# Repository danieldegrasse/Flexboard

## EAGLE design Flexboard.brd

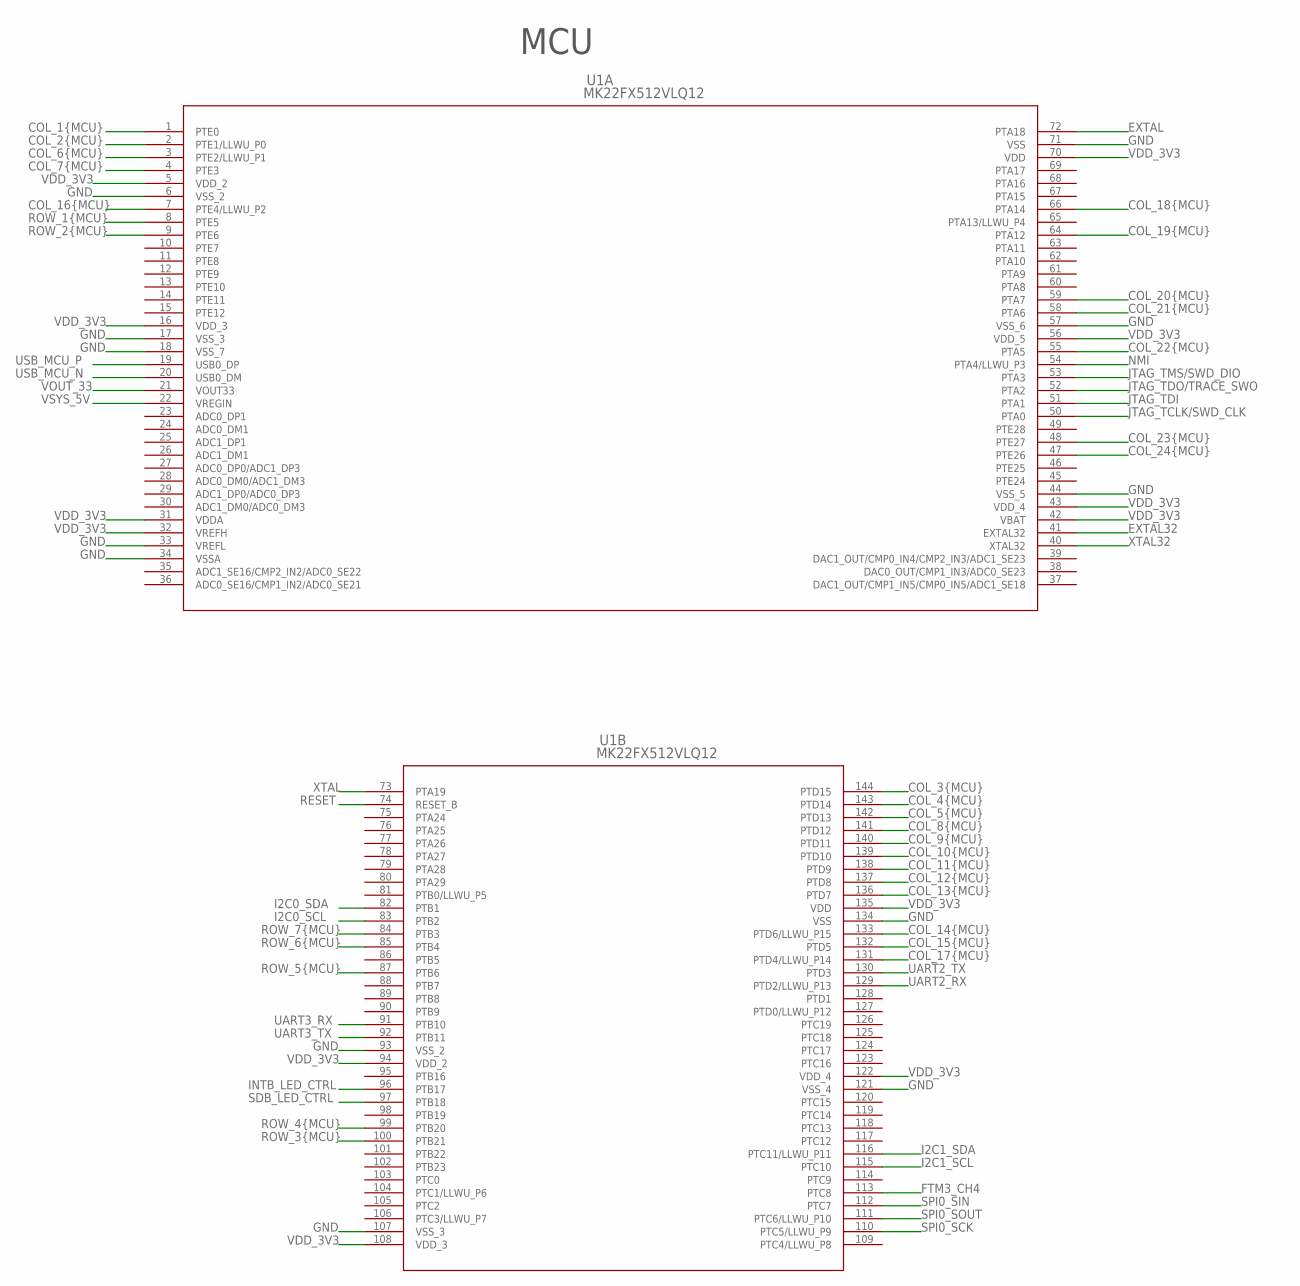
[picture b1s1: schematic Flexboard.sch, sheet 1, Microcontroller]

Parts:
U1: MK22FX512VLQ12; LQFP-144_20X20X1.6

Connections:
COL_1{MCU}: U1.1 (PTE0); also elsewhere on the board
COL_2{MCU}: U1.2 (PTE1/LLWU_P0); also elsewhere on the board
COL_3{MCU}: U1.144 (PTD15); also elsewhere on the board
COL_4{MCU}: U1.143 (PTD14); also elsewhere on the board
COL_5{MCU}: U1.142 (PTD13); also elsewhere on the board
COL_6{MCU}: U1.3 (PTE2/LLWU_P1); also elsewhere on the board
COL_7{MCU}: U1.4 (PTE3); also elsewhere on the board
COL_8{MCU}: U1.141 (PTD12); also elsewhere on the board
COL_9{MCU}: U1.140 (PTD11); also elsewhere on the board
COL_10{MCU}: U1.139 (PTD10); also elsewhere on the board
COL_11{MCU}: U1.138 (PTD9); also elsewhere on the board
COL_12{MCU}: U1.137 (PTD8); also elsewhere on the board
COL_13{MCU}: U1.136 (PTD7); also elsewhere on the board
COL_14{MCU}: U1.133 (PTD6/LLWU_P15); also elsewhere on the board
COL_15{MCU}: U1.132 (PTD5); also elsewhere on the board
COL_16{MCU}: U1.7 (PTE4/LLWU_P2); also elsewhere on the board
COL_17{MCU}: U1.131 (PTD4/LLWU_P14); also elsewhere on the board
COL_18{MCU}: U1.66 (PTA14); also elsewhere on the board
COL_19{MCU}: U1.64 (PTA12); also elsewhere on the board
COL_20{MCU}: U1.59 (PTA7); also elsewhere on the board
COL_21{MCU}: U1.58 (PTA6); also elsewhere on the board
COL_22{MCU}: U1.55 (PTA5); also elsewhere on the board
COL_23{MCU}: U1.48 (PTE27); also elsewhere on the board
COL_24{MCU}: U1.47 (PTE26); also elsewhere on the board
EXTAL: U1.72 (PTA18); also elsewhere on the board
EXTAL32: U1.41 (EXTAL32); also elsewhere on the board
FTM3_CH4: U1.113 (PTC8); also elsewhere on the board
GND: U1.6 (VSS_2), U1.17 (VSS_3), U1.18 (VSS_7), U1.33 (VREFL), U1.34 (VSSA), U1.44 (VSS_5), U1.57 (VSS_6), U1.71 (VSS), U1.93 (VSS_2), U1.107 (VSS_3), U1.121 (VSS_4), U1.134 (VSS); also elsewhere on the board
I2C0_SCL: U1.83 (PTB2); also elsewhere on the board
I2C0_SDA: U1.82 (PTB1); also elsewhere on the board
I2C1_SCL: U1.115 (PTC10); also elsewhere on the board
I2C1_SDA: U1.116 (PTC11/LLWU_P11); also elsewhere on the board
INTB_LED_CTRL: U1.96 (PTB17); also elsewhere on the board
JTAG_TCLK/SWD_CLK: U1.50 (PTA0); also elsewhere on the board
JTAG_TDI: U1.51 (PTA1); also elsewhere on the board
JTAG_TDO/TRACE_SWO: U1.52 (PTA2); also elsewhere on the board
JTAG_TMS/SWD_DIO: U1.53 (PTA3); also elsewhere on the board
NMI: U1.54 (PTA4/LLWU_P3); also elsewhere on the board
RESET: U1.74 (RESET_B); also elsewhere on the board
ROW_1{MCU}: U1.8 (PTE5); also elsewhere on the board
ROW_2{MCU}: U1.9 (PTE6); also elsewhere on the board
ROW_3{MCU}: U1.100 (PTB21); also elsewhere on the board
ROW_4{MCU}: U1.99 (PTB20); also elsewhere on the board
ROW_5{MCU}: U1.87 (PTB6); also elsewhere on the board
ROW_6{MCU}: U1.85 (PTB4); also elsewhere on the board
ROW_7{MCU}: U1.84 (PTB3); also elsewhere on the board
SDB_LED_CTRL: U1.97 (PTB18); also elsewhere on the board
SPI0_SCK: U1.110 (PTC5/LLWU_P9); also elsewhere on the board
SPI0_SIN: U1.112 (PTC7); also elsewhere on the board
SPI0_SOUT: U1.111 (PTC6/LLWU_P10); also elsewhere on the board
UART2_RX: U1.129 (PTD2/LLWU_P13); also elsewhere on the board
UART2_TX: U1.130 (PTD3); also elsewhere on the board
UART3_RX: U1.91 (PTB10); also elsewhere on the board
UART3_TX: U1.92 (PTB11); also elsewhere on the board
USB_MCU_N: U1.20 (USB0_DM); also elsewhere on the board
USB_MCU_P: U1.19 (USB0_DP); also elsewhere on the board
VDD_3V3: U1.5 (VDD_2), U1.16 (VDD_3), U1.31 (VDDA), U1.32 (VREFH), U1.42 (VBAT), U1.43 (VDD_4), U1.56 (VDD_5), U1.70 (VDD), U1.94 (VDD_2), U1.108 (VDD_3), U1.122 (VDD_4), U1.135 (VDD); also elsewhere on the board
VOUT_33: U1.21 (VOUT33); also elsewhere on the board
VSYS_5V: U1.22 (VREGIN); also elsewhere on the board
XTAL: U1.73 (PTA19); also elsewhere on the board
XTAL32: U1.40 (XTAL32); also elsewhere on the board

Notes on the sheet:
MCU

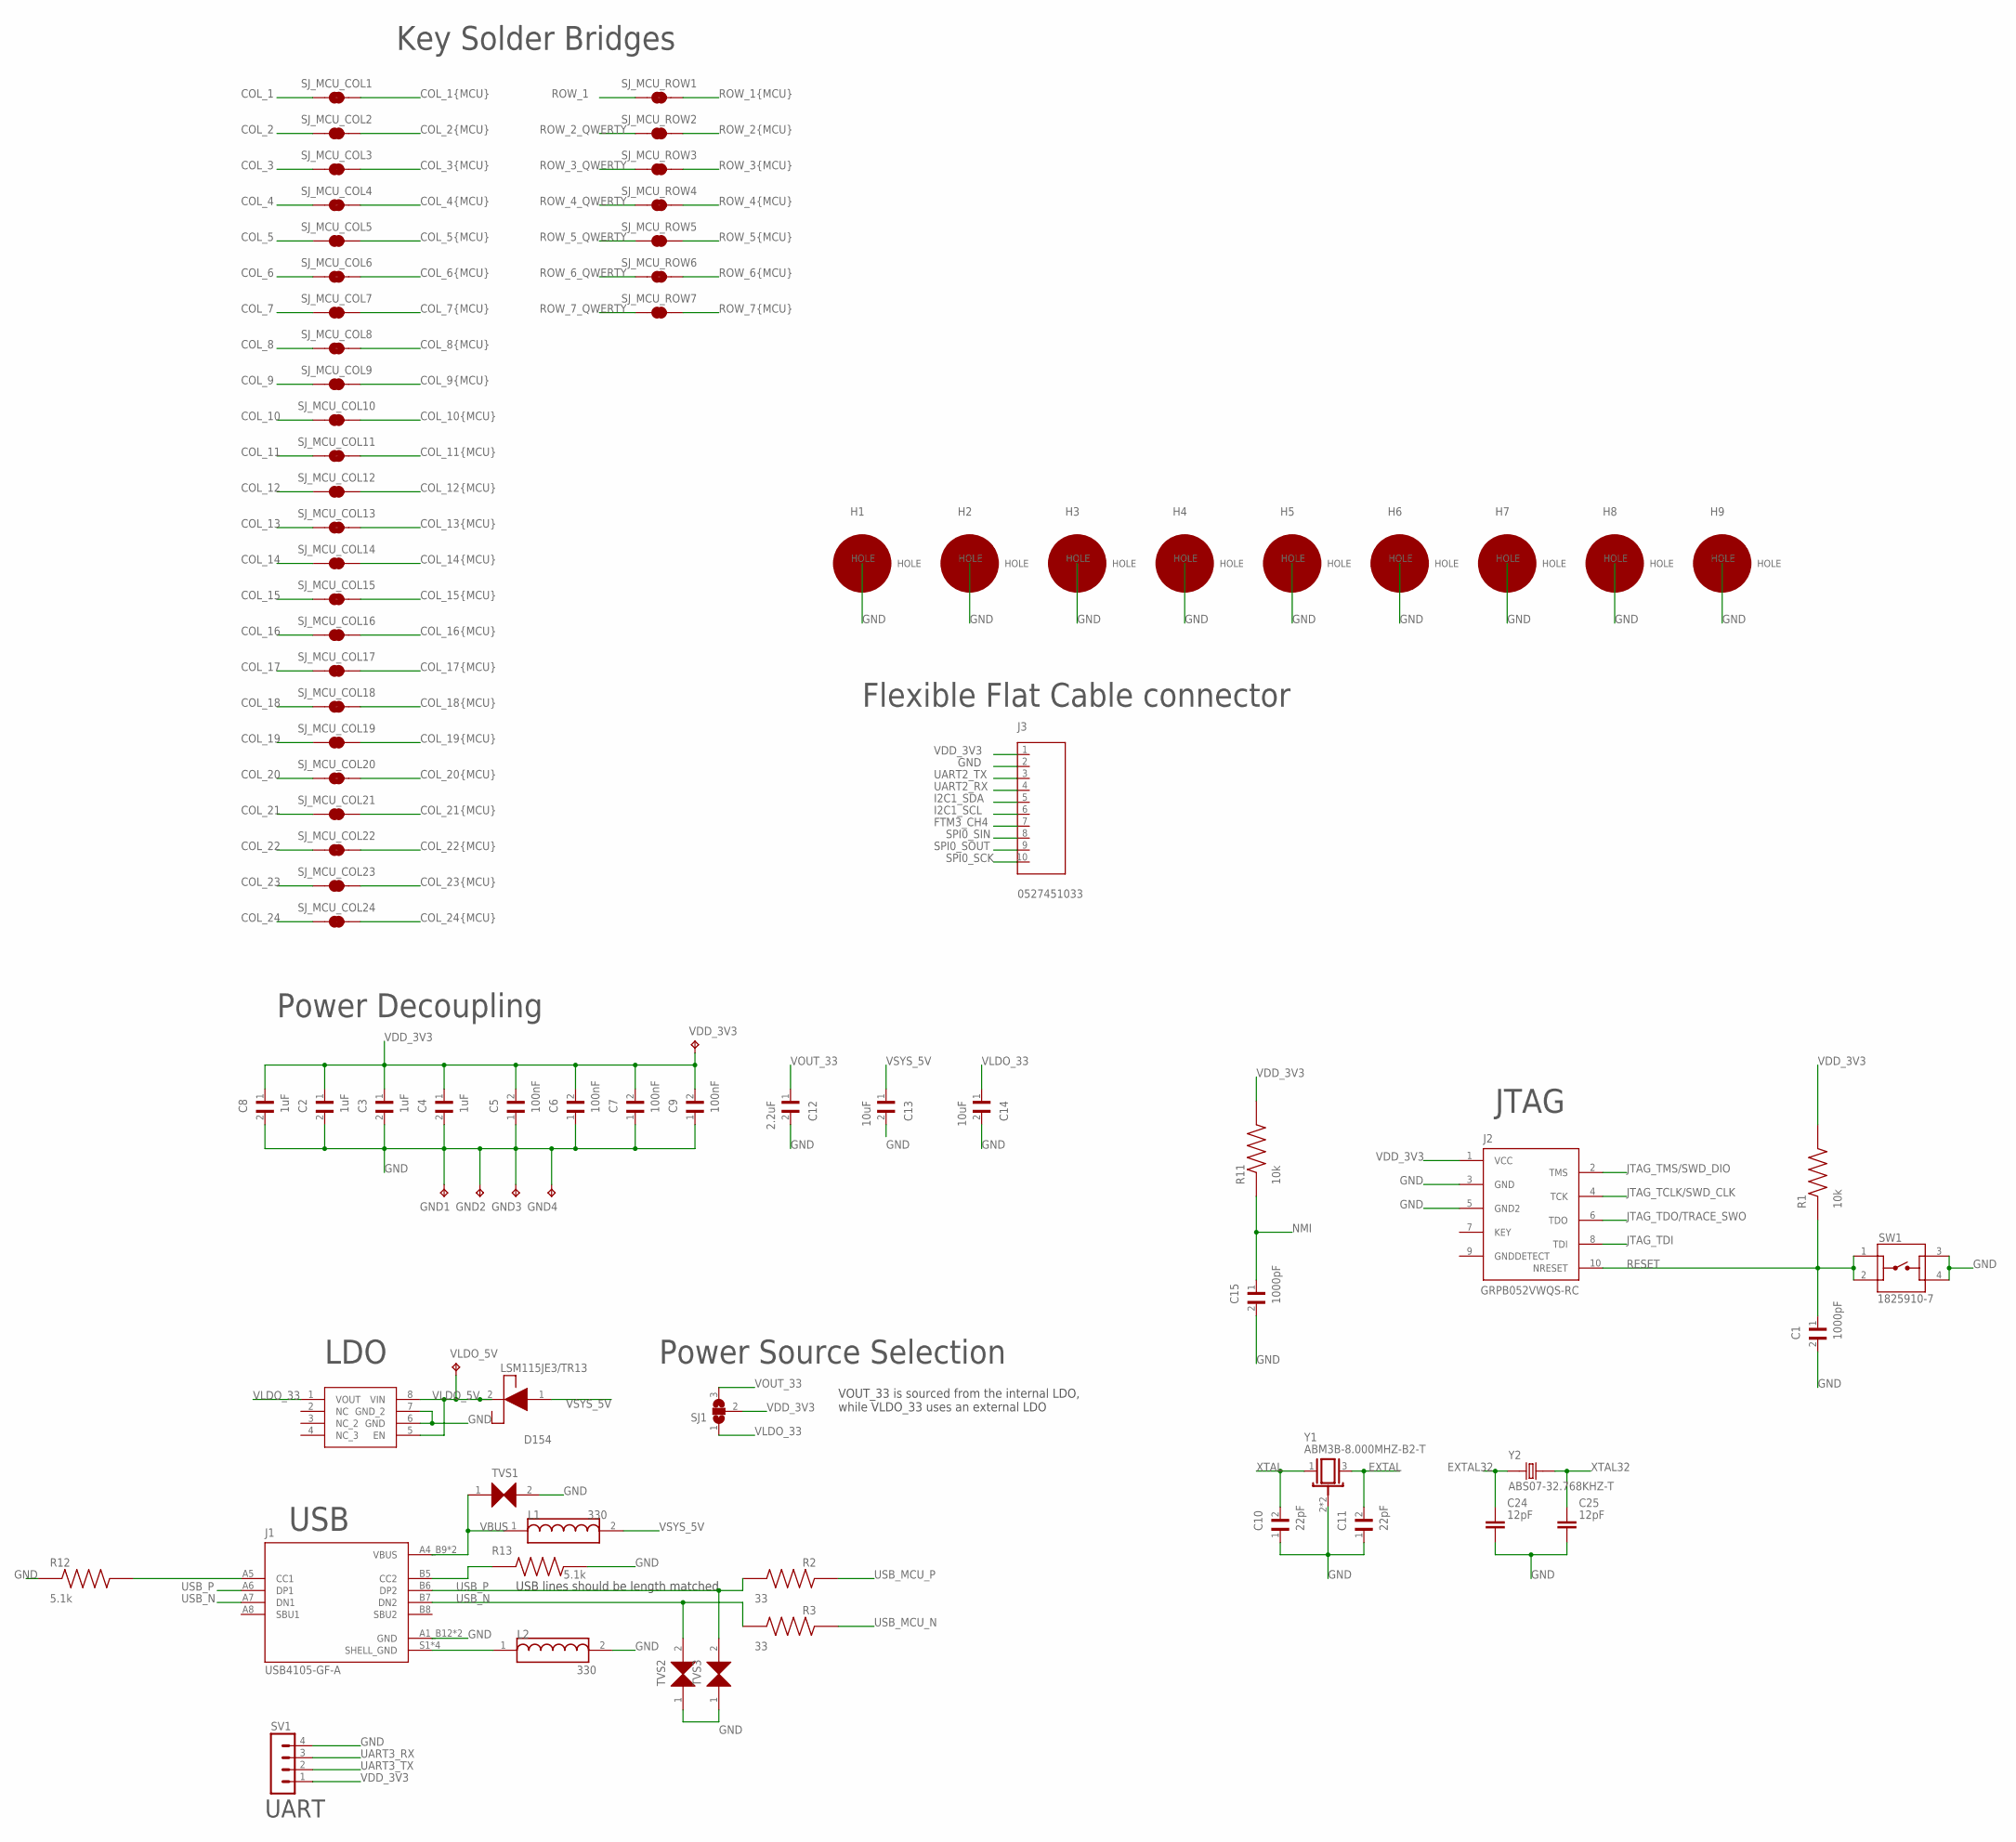
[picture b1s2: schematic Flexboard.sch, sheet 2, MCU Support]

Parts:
C1, C15: 1000pF; CAPC3216X110N
C2, C3, C4, C8: 1uF; CAPC3216X125N
C5, C6, C7, C9: 100nF; CAPC3216X88N
C10, C11: 22pF; CAPC3216X110N
C12: 2.2uF; CAPC3216X178N
C13, C14: 10uF; CAPC2012X145N
C24, C25: 12pF; CAPC2012X110
D154: LSM115JE3/TR13
GND1, GND2, GND3, GND4: TPB2,54; B2,54
H1, H2, H3, H4, H5, H6, H7, H8, H9: PTH
J1: USB4105-GF-A; GCT_USB4105-GF-A
J2: GRPB052VWQS-RC; DEBUG
J3: 0527451033; 52745-1033
L1, L2: 330; 78285333
R1, R11: 10k; RESC3115X65N
R2, R3: 33; RESC2012X65N
R12, R13: 5.1k; RESC2012X60N
SJ1: SJ2W; SJ_2
SJ_MCU_COL1, SJ_MCU_COL2, SJ_MCU_COL3, SJ_MCU_COL4, SJ_MCU_COL5, SJ_MCU_COL6, SJ_MCU_COL7, SJ_MCU_COL8, SJ_MCU_COL9, SJ_MCU_COL10, SJ_MCU_COL11, SJ_MCU_COL12, SJ_MCU_COL13, SJ_MCU_COL14, SJ_MCU_COL15, SJ_MCU_COL16, SJ_MCU_COL17, SJ_MCU_COL18, SJ_MCU_COL19, SJ_MCU_COL20, SJ_MCU_COL21, SJ_MCU_COL22, SJ_MCU_COL23, SJ_MCU_COL24: JUMPER-SMT_2_NC_TRACE_NO-SILK; SMT-JUMPER_2_NC_TRACE_NO-SILK
SJ_MCU_ROW1, SJ_MCU_ROW2, SJ_MCU_ROW3, SJ_MCU_ROW4, SJ_MCU_ROW5, SJ_MCU_ROW6, SJ_MCU_ROW7: JUMPER-SMT_2_NC_TRACE_NO-SILK; SMT-JUMPER_2_NC_TRACE_NO-SILK
SV1: MA04-1
SW1: 1825910-7; SW_1825910-7
TVS1, TVS2, TVS3: 0603ESDA2-TR2
U2: AP2115M-3.3TRG1; SOIC127P600X175-8N
VDD_3V3: TPB2,54; B2,54
VLDO_5V: TPB2,54; B2,54
Y1: ABM3B-8.000MHZ-B2-T; OSC_ABM3B-8.000MHZ-B2-T
Y2: ABS07-32.768KHZ-T; XTAL_ABS07-32.768KHZ-T

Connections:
COL_1: SJ_MCU_COL1.1; also elsewhere on the board
COL_1{MCU}: SJ_MCU_COL1.2; also elsewhere on the board
COL_2: SJ_MCU_COL2.1; also elsewhere on the board
COL_2{MCU}: SJ_MCU_COL2.2; also elsewhere on the board
COL_3: SJ_MCU_COL3.1; also elsewhere on the board
COL_3{MCU}: SJ_MCU_COL3.2; also elsewhere on the board
COL_4: SJ_MCU_COL4.1; also elsewhere on the board
COL_4{MCU}: SJ_MCU_COL4.2; also elsewhere on the board
COL_5: SJ_MCU_COL5.1; also elsewhere on the board
COL_5{MCU}: SJ_MCU_COL5.2; also elsewhere on the board
COL_6: SJ_MCU_COL6.1; also elsewhere on the board
COL_6{MCU}: SJ_MCU_COL6.2; also elsewhere on the board
COL_7: SJ_MCU_COL7.1; also elsewhere on the board
COL_7{MCU}: SJ_MCU_COL7.2; also elsewhere on the board
COL_8: SJ_MCU_COL8.1; also elsewhere on the board
COL_8{MCU}: SJ_MCU_COL8.2; also elsewhere on the board
COL_9: SJ_MCU_COL9.1; also elsewhere on the board
COL_9{MCU}: SJ_MCU_COL9.2; also elsewhere on the board
COL_10: SJ_MCU_COL10.1; also elsewhere on the board
COL_10{MCU}: SJ_MCU_COL10.2; also elsewhere on the board
COL_11: SJ_MCU_COL11.1; also elsewhere on the board
COL_11{MCU}: SJ_MCU_COL11.2; also elsewhere on the board
COL_12: SJ_MCU_COL12.1; also elsewhere on the board
COL_12{MCU}: SJ_MCU_COL12.2; also elsewhere on the board
COL_13: SJ_MCU_COL13.1; also elsewhere on the board
COL_13{MCU}: SJ_MCU_COL13.2; also elsewhere on the board
COL_14: SJ_MCU_COL14.1; also elsewhere on the board
COL_14{MCU}: SJ_MCU_COL14.2; also elsewhere on the board
COL_15: SJ_MCU_COL15.1; also elsewhere on the board
COL_15{MCU}: SJ_MCU_COL15.2; also elsewhere on the board
COL_16: SJ_MCU_COL16.1; also elsewhere on the board
COL_16{MCU}: SJ_MCU_COL16.2; also elsewhere on the board
COL_17: SJ_MCU_COL17.1; also elsewhere on the board
COL_17{MCU}: SJ_MCU_COL17.2; also elsewhere on the board
COL_18: SJ_MCU_COL18.1; also elsewhere on the board
COL_18{MCU}: SJ_MCU_COL18.2; also elsewhere on the board
COL_19: SJ_MCU_COL19.1; also elsewhere on the board
COL_19{MCU}: SJ_MCU_COL19.2; also elsewhere on the board
COL_20: SJ_MCU_COL20.1; also elsewhere on the board
COL_20{MCU}: SJ_MCU_COL20.2; also elsewhere on the board
COL_21: SJ_MCU_COL21.1; also elsewhere on the board
COL_21{MCU}: SJ_MCU_COL21.2; also elsewhere on the board
COL_22: SJ_MCU_COL22.1; also elsewhere on the board
COL_22{MCU}: SJ_MCU_COL22.2; also elsewhere on the board
COL_23: SJ_MCU_COL23.1; also elsewhere on the board
COL_23{MCU}: SJ_MCU_COL23.2; also elsewhere on the board
COL_24: SJ_MCU_COL24.1; also elsewhere on the board
COL_24{MCU}: SJ_MCU_COL24.2; also elsewhere on the board
EXTAL: C11.2, Y1.3; also elsewhere on the board
EXTAL32: C24.1, Y2.1; also elsewhere on the board
FTM3_CH4: J3.7; also elsewhere on the board
GND: C1.2, C2.2, C3.2, C4.2, C5.1, C6.1, C7.1, C8.2, C9.1, C10.1, C11.1, C12.2, C13.2, C14.2, C15.2, C24.2, C25.2, GND1.TP, GND2.TP, GND3.TP, GND4.TP, H1.HOLE, H2.HOLE, H3.HOLE, H4.HOLE, H5.HOLE, H6.HOLE, H7.HOLE, H8.HOLE, H9.HOLE, J1.A1_B12 (GND), J1.B1_A12 (GND), J2.3 (GND), J2.5 (GND2), J3.2, L2.2, R12.1, R13.2, SV1.4, SW1.3, SW1.4, TVS1.2, TVS2.1, TVS3.1, U2.6 (GND), U2.7 (GND_2), Y1.2 (GND), Y1.4 (GND); also elsewhere on the board
I2C1_SCL: J3.6; also elsewhere on the board
I2C1_SDA: J3.5; also elsewhere on the board
JTAG_TCLK/SWD_CLK: J2.4 (TCK); also elsewhere on the board
JTAG_TDI: J2.8 (TDI); also elsewhere on the board
JTAG_TDO/TRACE_SWO: J2.6 (TDO); also elsewhere on the board
JTAG_TMS/SWD_DIO: J2.2 (TMS); also elsewhere on the board
unnamed: J1.S1 (SHELL_GND), J1.S2 (SHELL_GND), J1.S3 (SHELL_GND), J1.S4 (SHELL_GND), L2.1
unnamed: J1.B5 (CC2), R13.1
unnamed: J1.A5 (CC1), R12.2
NMI: C15.1, R11.1; also elsewhere on the board
RESET: C1.1, J2.10 (NRESET), R1.1, SW1.1, SW1.2; also elsewhere on the board
ROW_1: SJ_MCU_ROW1.1; also elsewhere on the board
ROW_1{MCU}: SJ_MCU_ROW1.2; also elsewhere on the board
ROW_2_QWERTY: SJ_MCU_ROW2.1; also elsewhere on the board
ROW_2{MCU}: SJ_MCU_ROW2.2; also elsewhere on the board
ROW_3_QWERTY: SJ_MCU_ROW3.1; also elsewhere on the board
ROW_3{MCU}: SJ_MCU_ROW3.2; also elsewhere on the board
ROW_4_QWERTY: SJ_MCU_ROW4.1; also elsewhere on the board
ROW_4{MCU}: SJ_MCU_ROW4.2; also elsewhere on the board
ROW_5_QWERTY: SJ_MCU_ROW5.1; also elsewhere on the board
ROW_5{MCU}: SJ_MCU_ROW5.2; also elsewhere on the board
ROW_6_QWERTY: SJ_MCU_ROW6.1; also elsewhere on the board
ROW_6{MCU}: SJ_MCU_ROW6.2; also elsewhere on the board
ROW_7_QWERTY: SJ_MCU_ROW7.1; also elsewhere on the board
ROW_7{MCU}: SJ_MCU_ROW7.2; also elsewhere on the board
SPI0_SCK: J3.10; also elsewhere on the board
SPI0_SIN: J3.8; also elsewhere on the board
SPI0_SOUT: J3.9; also elsewhere on the board
UART2_RX: J3.4; also elsewhere on the board
UART2_TX: J3.3; also elsewhere on the board
UART3_RX: SV1.3; also elsewhere on the board
UART3_TX: SV1.2; also elsewhere on the board
USB_MCU_N: R3.2; also elsewhere on the board
USB_MCU_P: R2.2; also elsewhere on the board
USB_N: J1.A7 (DN1), J1.B7 (DN2), R3.1, TVS2.2
USB_P: J1.A6 (DP1), J1.B6 (DP2), R2.1, TVS3.2
VBUS: J1.A4_B9 (VBUS), J1.B4_A9 (VBUS), L1.1, TVS1.1
VDD_3V3: C2.1, C3.1, C4.1, C5.2, C6.2, C7.2, C8.1, C9.2, J2.1 (VCC), J3.1, R1.2, R11.2, SJ1.2, SV1.1, VDD_3V3.TP; also elsewhere on the board
VLDO_5V: D154.2 (CATHODE), U2.5 (EN), U2.8 (VIN), VLDO_5V.TP; also elsewhere on the board
VLDO_33: C14.1, SJ1.1, U2.1 (VOUT)
VOUT_33: C12.1, SJ1.3; also elsewhere on the board
VSYS_5V: C13.1, D154.1 (ANODE), L1.2; also elsewhere on the board
XTAL: C10.2, Y1.1; also elsewhere on the board
XTAL32: C25.1, Y2.2; also elsewhere on the board

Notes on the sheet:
USB
Key Solder Bridges
JTAG
UART
Power Source Selection
Power Decoupling
LDO
VOUT_33 is sourced from the internal LDO, while VLDO_33 uses an external LDO
USB lines should be length matched
Flexible Flat Cable connector

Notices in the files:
parts and their libraries:
SparkFun-Jumpers: Licensing: Creative Commons ShareAlike 4.0 International - https://creativecommons.org/licenses/by-sa/4.0
